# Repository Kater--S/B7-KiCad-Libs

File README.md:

# B7-KiCad-Libs

Basis-Repository für die B7-Elektronikentwicklung

## Komponenten:

1. **KiCad** als Entwicklungsplattform für Elektronik
	* Projekte jeweils als GitHub-Repo
	* aktuelle Version 9 wird vorausgesetzt
	* JLCPCB Fabrication Toolkit soll verwendet werden
2. **eigene Libs** für Symbole und Footprints
	* je 1 Lib, keine Unteraufteilung
	* beide zusammen als gemeinsames GitHub-Repo
	* = dieses Repository
3. **PartDB** zur Verwaltung der eingesetzten Bauelemente
	* PartDB aktuell von Mike gehostet, später auf B7-Server
	* Anbindung an DigiKey, LCSC und andere Supplier
	* Symbole und Footprints als textueller(!) Verweis in B7-Libs
	* TBD: _immer_ eigenes Symbol und Footprint, KiCad-Libs werden nicht genutzt

## Einrichtung:

1. KiCad installieren (für alle Benutzer auf dem Computer)
2. JLCPCB Fabrication Toolkit installieren (pro Benutzer)
3. gepatchte Datei `process.py` aus dem Repo unter `${KICAD_3RD_PARTY}/plugins/com_github_bennymeg_JLC-Plugin-for-KiCad` kopieren (bezieht sich auf den Stand der Datei vom 2025-04-30, enthalten im Release v5.1.0 des Plugins)
4. PartDB-Account anlegen und API Key generieren
5. B7-Libs-Repo aus GitHub clonen nach `${KICAD_3RD_PARTY}`, d.h. dieses README.md liegt dann unter `${KICAD_3RD_PARTY}/B7-KiCad-Libs/README.md`
6. In `libs`: Template für `partd.kicad_httplib` kopieren und API Key aus PartDB eintragen
7. Ein Projekt öffnen, etwa `test/B7Test` oder `template/B7Template`
	- Darin sind die passenden Library-Einstellungen bereits vorgenommen:
		- in KiCad: Preferences → Manage Symbol Libraries…:
			- Project Specific Library `B7_Symbols` als Typ `KiCad` eintragen, Pfad ist `${KICAD_3RD_PARTY}/B7-KiCad-Libs/libs/B7.kicad_sym`; Description ist `B7 symbols`
			- Project Specific Library `B7_PartDB` als Typ `HTTP` eintragen, Pfad ist `${KICAD_3RD_PARTY}/B7-KiCad-Libs/libs/B7.kicad_sym`; Description ist `B7 PartDB`
		- in KiCad: Preferences → Manage Footprint Libraries…:
			- Project Specific Library `B7_Footprints` als Typ KiCad eintragen, Pfad ist `${KICAD_3RD_PARTY}/B7-KiCad-Libs/libs/B7.pretty`; Description ist `B7 footprints`
			- (PartDB-Anbindung gibt es hier nicht)
8. Eigene Projekte können aus dem Template-Projekt erstellt werden.
	- Wenn ein B7-Projekt als eigenes Repo gespeichert wird, müssen die Einstellungen wie beschrieben sein.

## Offene Punkte

- Aufteilung entspricht nicht den Default-Pfaden von KiCad (z.B. macOS: `~/Documents/KiCad/9.0/{symbols,footprints,projects}`). 
  Es sollte aber in Ordnung sein, dass Projekte (und Libs) auch außerhalb der Standardpfade liegen.
- Quer-Abhängigkeiten bei Pfaden müssen funktionieren
	- auch auf unterschiedlichen Plattformen (Linux, macOS, Windows)
	- auch mit abweichenden Speicherorten
	- → Verwendung von Environmentvariablen, wo möglich
	- Dies ist derzeit durch Verwendung von `${KICAD_3RD_PARTY}/`… gegeben
- TBD, ob die B7-Libs global oder projektspezifisch sein sollten
	- pro projektspezifisch: kein manuelles Setup notwendig, wenn Template verwendet oder bestehendes Projekt geladen wird
	- pro global: kein Setup notwendig bei Neuerstellung eines Projekts
	- aktuell implementiert: projektspezifisch
- Mechanismus zur Übernahme der LCSC-/JLCPCB-Teilenummer → PartDB und weiter von PartDB → KiCad – so, dass das Fabrication Toolkit sie erkennt und nutzt 
  → derzeit im ersten Schritt manueller Eintrag und im zweiten Schritt durch Patch des Plugins.
- Noch zu klären: Wie funktioniert die Definition von Array-Bauteilen, also bspw. Widerstandsarrays oder Mehrfachgattern?
- Noch zu testen: Kompletter Workflow bis hin zu den erzeugten Artefakten für die Produktion.

## Verwendung

- Projekt anlegen: Template-Projekt laden, mit *File → Save As…* als neues Projekt speichern und dies als Repository anlegen
- vorhandenes B7-Bauteil verwenden: auswählen aus B7-Lib
- neues B7-Bauteil anlegen: siehe folgenden Abschnitt

## Neues Bauteil anlegen

Vorausgesetzt wird eine Liste der einzupflegenden Bauteile. Darin könnten Einträge wie folgt aussehen:

|**lfd. Nr.**|**Hersteller- Typbezeichnung**|**Hersteller**|**Kurzbeschreibung**|**Kategorie**|**PartDB**|**Symbol**|**Footprint**|**LCSC Part#**|**Datenblatt**|
|---|---|---|---|---|---|---|---|---|---|
|10|CPDT6-5V0UPC-HF|Comchip|4 fach ESD Schutzarray 5V Dioden mit Sammelschiene|Halbleiter||||C2443674|CPDT6-5V0UPC-HF RevB242302.pdf|
|11|TMUX1204DQAR|Texas Instruments|4:1 Multiplexer 5V, 5Ohm|Halbleiter||||C1849379|TMUX1204.pdf|
|12|PI6ULS5V9617AUEX|Diodes Inc.|I2C Bus Repeater|Halbleiter||||C526728|PI6ULS5V9617C.pdf|

Exemplarisch soll das ESD-Schutzarray aus Zeile 10 ( = lfd.Nr.) eingepflegt werden. Dies ist nicht die interne PartDB-ID, denn diese wird von PartDB eigenständig fortlaufend vergeben und kann daher nicht vorab festgelegt werden! Diese lfd. Nr. wird nicht weiter verwendet, denn es gibt ohnehin schon die interne ID, die LCSC Part# sowie die Hersteller-Typbezeichnung.

**Vorschläge:** 
- Die Spalte mit der lfd. Nr. kann im Prinzip entfallen, da im Rechenblatt die Zeilen ohnehin nummeriert sind. 
- Es sollte zusätzlich eine Spalte *Prefix* geben, in der der Präfix-Buchstabe für das Bauelement aufgeführt ist (R für Widerstände, U für ICs, D für Dioden usw.), da es nicht immer eindeutig ist, wie der Buchstabe lauten sollte.

### PartDB

In der Oberfläche von PartDB wird jetzt aus der linken Seitenleiste *Tools → Create parts from info provider* geklickt. 

Im entsprechenden Formular wird unter *Keyword* die LCSC-Teilenummer `C2443674` eingetragen und unter *Providers* `LCSC`. Ein Klick auf den Button *Search* listet als Resultat das gewünschte Bauteil.

Mit dem Button *+* am rechten Ende der Zeile wird ein Dialog *Create new part* aufgelegt, bei dem das Formular mit den Informationen der LCSC-Website gefüllt wurde. Die einzelnen Felder können jetzt auf Plausibilität/Korrektheit geprüft werden.

Als interne PartDB-ID werde hier beispielsweise die 7 zugeteilt. Im Webformular steht diese Nummer dann oben rechts in der Titelzeile des blauen Bereichs, in Klammern gefolgt von der noch einzutragenen IPN (siehe unten). In der Listenansicht über die Kategorien können mit dem Zahnrad-Aufklappmenü die Felder *ID* und *IPN* aktiviert werden, wenn gewünscht.

Unter *Category* muss die Bauteil-Kategorie angegeben werden. Vorgeschlagen wird der Wert, den der Provider LCSC verwendet: `Circuit Protection -> ESD and Surge Protection (TVS -> ESD)` – wenn dieser String in das Feld kopiert wird, wird in einem Popup vorgeschlagen, die Kategorie anzulegen. Im vorliegenden Fall gibt es ein kleines Problem, weil der Pfeil `->` von PartDB als Ebenentrenner aufgefasst wird, hier kommt er aber beim zweiten Auftreten in den Klammern als Text vor. Dies könnte durch Ändern in `→` umgangen werden, der Eintrag lautet damit also `Circuit Protection -> ESD and Surge Protection (TVS → ESD)`. Allerdings gibt es mit Unicode-Sonderzeichen teilweise Probleme, insofern wäre es sicherer, anstelle `→` hier einfach `/` zu verwenden: `Circuit Protection -> ESD and Surge Protection (TVS / ESD)`. Es wird damit also eine Hauptkategorie `Circiot Protection` angelegt und darunter eine Subkategorie `ESD and Surge Protection (TVS / ESD)`. Darin wird das neue Bauteil einsortiert.

Unter *Internal Part Number (IPN)* wird noch die `C2443674`, also die LCSC-Teilenummer aus unserer Tabelle, eingetragen. Das gepatchte Fabrication Toolkit übernimmt dieses Feld, das in KiCad als *Part-DB IPN* erscheint, später als *LCSC Part #* in die BOM (Datei `bom.csv`).

Unter *Attachments* kann als *Preview Image* ein Foto ausgewählt werden, falls vorhanden (hier gibt es keins). Unter *EDA Information* kann noch als *Reference prefix* z.B. `U` (oder `D`??) eingetragen werden, ein *Value* wird hier nicht benötigt. Es fehlen nun noch das *KiCad schematic symbol* und der *KiCad footprint*.

### KiCad

In den von LCSC importierten Information (und auch im verlinkten Datenblatt) findet sich als Footprint das Gehäuse `SOT-23-6`. 

KiCad wird nun beispielsweise mit dem Test-Projekt geöffnet, so dass die B7-Libs konfiguriert sind. 

Im Symbol Editor muss nun nach Möglichkeit ein passendes Schaltplansymbol gefunden werden. Mit den Informationen aus dem Datenblatt erscheint eine Suche nach `diode` hilfreich. Wenn man mit dem Mauscursor über einem Listeneintrag stehenbleibt, erscheint nach einer Weile ein Vorschaubild des entsprechenden Symbols. Wenn die Liste unter dem Mauscursor durchgescrollt wird, wechselt das Vorschaubild entsprechend, und man kann schnell eine größere Anzahl von Einträgen durchsehen. Im Falle des gesuchten Bauteils findet sich ein passendes Symbol in der Standardbibliothek `Power_Protection` unter dem Namen `NUP4202`; dieses wird nun geöffnet und mittels *File* → *Save As…* wird dieser Footprint mit dem Namen `CPDT6-5V0UPC-HF` in die Bibliothek `B7_Footprints` gespeichert. **Achtung:** Mit diesem Symbol ist bereits ein Standard-Footprint assoziiert. Dieser wird bei der Bauteildefinition in PartDB aber durch einen eigenen aus der B7-Footprint-Library ersetzt (der durchaus identisch aussehen kann).

Im Footprint Editor wird daher nun nach `SOT-23-6` gesucht, ein passender Eintrag findet sich in der Standardbibliothek `Package_TO_SOT_SMD` und kann mit Doppelklick geöffnet werden. Unter *File* → *Save As…* wird dieser Footprint nun in die Bibliothek `B7_Footprints` gespeichert.

### PartDB

Im PartDB-Formular wird entsprechend nun unter *KiCad schematic symbol* `B7_Symbols:CPDT6-5V0UPC-HF` eingetragen.

Unter *KiCad footprint* wird analog `B7_Footprints:SOT-23-6` eingetragen.

**Wichtig:** *Diese Einträge sind case-sensitive, d.h. wenn irrtümlich etwa `B7_footprints` angegeben wird, findet KiCad den Footprint nicht.*

**Problem:**
Es fehlt noch die LCSC-Teilenummer. Diese ist in PartDB bekannt, wird aber offenbar nicht über das API in KiCad übernommen. Manuell kann sie auf KiCad-Seite auch nicht eingetragen werden, weil die B7_PartDB-Library read-only ist, d.h. Änderungen können nur auf PartDB-Seite vorgenommen werden.

Aus diesem Grund kann jetzt manuell aus der Gruppe *Purchase information* unter *Supplier* `LCSC` der Wert des Feldes *Supplier part number*, hier im Beispiel also `C2443674`, kopiert und in der Gruppe *Advanced* in das Feld *Internal Part Number (IPN)* eingetragen werden. Alternativ kann dies mit dem **PartDB Helper** (s.u.) zu einem späteren Zeitpunkt für alle Bauteile erfolgen, bei denen der IPN-Eintrag noch fehlt.

Mit dem Button *Save changes* wird die Transaktion abgeschlossen.

### KiCad

Im Testprojekt kann in KiCad nun geprüft werden, ob das Bauteil korrekt angelegt wurde:

Im Schaltplaneditor wird *Place Symbols* (Taste A) aufgerufen und in der Suchmaske `CPDT` eingegeben. Als Fundstelle wird – neben der reinen Symbol-Bibliothek `B7_Symbols` – die PartDB-Bibliothek `B7_PartDB - Circuit Protection` angegeben, also mit der Unterkategorie der ersten Stufe; tiefere Stufen werden hier nicht angezeigt, die Einträge stehen alle in der Unterkategorie der ersten Stufe. Dort gibt es den Eintrag `CPDT6-5V0UPC-HF` mit passendem Symbol und Footprint in der Vorschau. Nach Bestätigen mit *OK* kann das Bauteil im Schaltplan platziert werden.

**Anmerkung:** Falls das Symbol im Schaltplan grau umrahmt und mit einem Symbol einer Welle (~) im Kreis angezeigt wird, liegt das daran, dass für das Bauteil das Merkmal *exclude from simulation* gesetzt und in KiCad der Menüpunkt *View → Mark items which are excluded from simulation* aktiv ist. Durch Deaktivieren des Menüpunkts kann der Marker unsichtbar geschaltet werden.

Ein Doppelklick auf das Symbol öffnet den Dialog *Symbol Properties*. Dort können die verschiedenen Parameter überprüft werden. Die LCSC-Teilenummer wird unter *Part-DB IPN* angezeigt.

Nach dem Wechseln auf den Platineneditor und einem *Update PCB from Schematic* (Taste F8) und dem entsprechenden Dialog erscheint der Footprint und kann platziert werden.

### Fabrication Toolkit

**Achtung:** Fabrication Toolkit findet in der offiziellen Version lediglich die MPN, also im Beispiel `CPDT6-5V0UPC-HF`, als vermeintliche LCSC Part Number. Hier ist die oben erwähnte Softwareanpassung des Plugins notwendig, damit stattdessen die IPN verwendet wird. Nach dem Patch wird nun zuerst das Feld *IPN* geprüft, erst danach die anderen.

Wenn es für das Plugin eine neue Version (> v5.1.0) gibt, muss der Patch nach einem Update mindestens erneut installiert werden, eventuell ist auch eine Anpassung notwendig.

Für PartDB wurde ein Issue eingestellt, das eine Funktion vorschlägt, um weitere Felder ins API zu übernehmen. Wenn dies implementiert wird, werden sowohl das manuelle Eintragen der Teilenummer als auch der Patch voraussichtlich überflüssig.

Im PCB-Editor von KiCad kann das Fabrication Toolkit über das entsprechende Icon aufgerufen werden. Es erscheint ein Dialog mit weiteren Optionen (siehe Dokumentation zum Toolkit) und einem Button *Generate*, über den die Erzeugung der Produktionsdateien gestartet wird.

#### Lösungsansatz: PartDB Helper

Ein externes Tool (PartDB Helper) wurde erstellt, das das PartDB-API verwendet, um halbautomatisch bei allen erfassten Bauteilen die LCSC-Bestellnummer in das Feld IPN einzutragen. Das Tool nutzt Flask und erfordert ein Token mit Edit-Berechtigung, um in PartDB die notwendigen Änderungen an den Bauteildaten durchführen zu können.

Außerdem kann das Tool verwendet werden, um Bauteile mit fehlenden Symbol- und Footprint-Einträgen zu finden.

Nähere Informationen im README und dem Benutzerhandbuch.

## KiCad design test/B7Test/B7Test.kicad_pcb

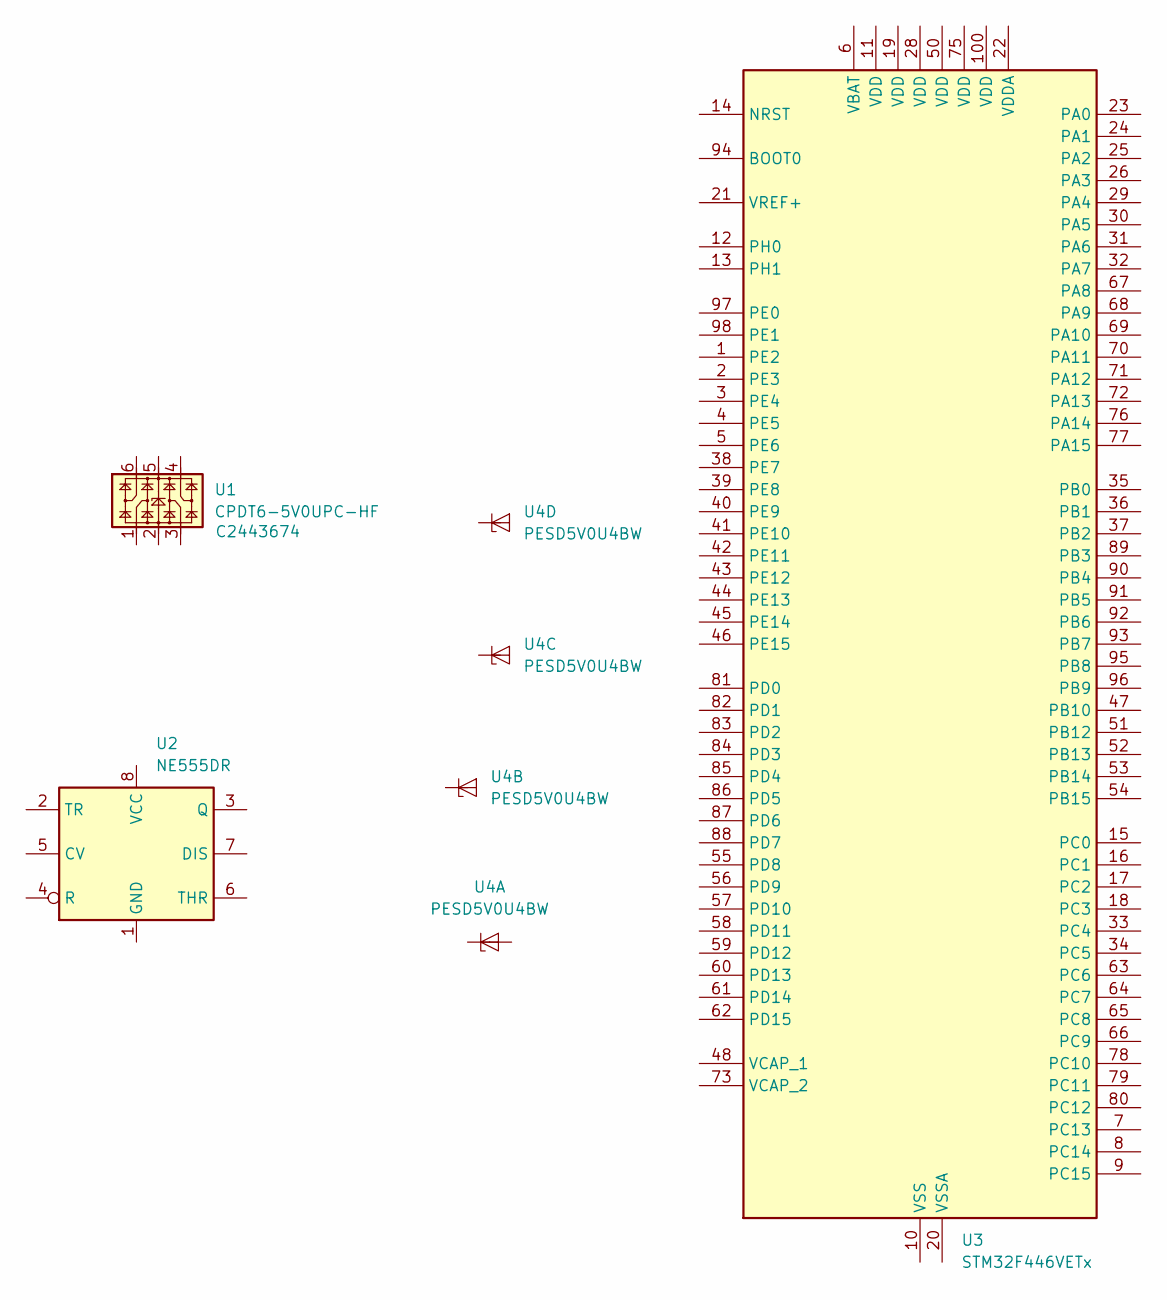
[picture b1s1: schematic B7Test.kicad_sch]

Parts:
U1: CPDT6-5V0UPC-HF; SOT-23-6; MPN CPDT6-5V0UPC-HF
U2: NE555DR; SOIC-8_3.9x4.9mm_P1.27mm; MPN NE555N-TD
U3: STM32F446VETx; LQFP-100_14x14mm_P0.5mm; MPN STM32F446VET6TR
U4: PESD5V0U4BW; SOT-665; MPN PESD5V0U4BW,115

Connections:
unnamed: U3.10 (VSS), U3.27 (VSS), U3.49 (VSS), U3.74 (VSS), U3.99 (VSS)
unnamed: U4.2 (A), U4.5 (A)

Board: 2 copper layers, 4 parts (0 on the bottom side), 2 nets, no tracks yet.

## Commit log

2025-05-31 Grundkonfiguration
2025-05-31 README
2025-05-31 ignore cache files
2025-05-31 Typo
2025-05-31 Fix: Layers, Sheets
2025-06-02 aktueller Stand
2025-06-02 Korrekturen und Ergänzungen
2025-06-03 add PartDB Helper tool
2025-06-03 README ergänzt
2025-06-03 Benutzerhandbuch
2025-06-06 Refresh button
2025-06-08 PartDB Helper improvements
    KiCad page, better formatting, parts link into PartDB
2025-06-08 B7 libs, test project
